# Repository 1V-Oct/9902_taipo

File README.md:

# TaiPo Micro MIDI Interface for 1V-Oct Family of Products
## Model: VO-9902 
## Version: 1.0

---
(C)2022 1V-Oct Limited

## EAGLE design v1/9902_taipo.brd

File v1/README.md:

# TaiPo Micro MIDI Interface for 1V-Oct Family of Products
## Model: VO-9902 
## Version: 1.0

This is simple MIDI interface for The Centre by 1V/Oct.

The 3.5mm jacks should be stereo jacks
PJ-301CM

Optocoupler:
TOSHIBA TLP2366 or can be the newer part TLP2361 (any other totem-pole octocoupler with 3.3V output can be used)

---
(C)2022 1V-Oct Limited

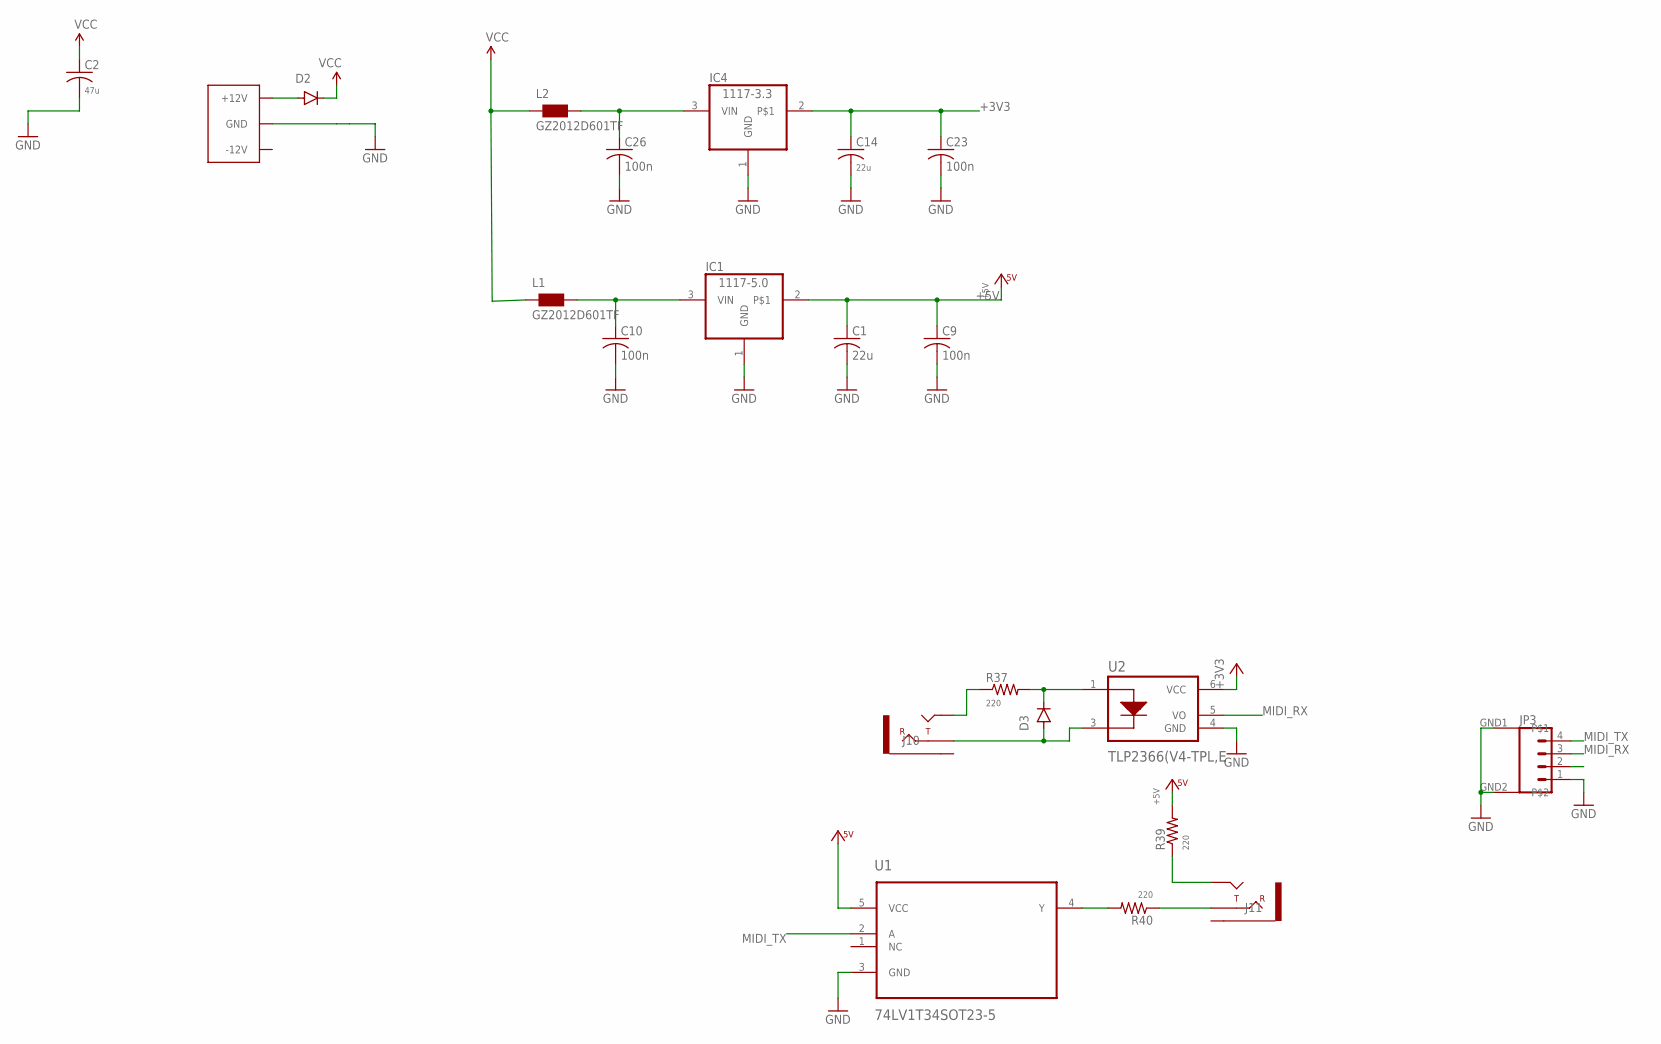
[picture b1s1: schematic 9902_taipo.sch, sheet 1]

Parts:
C1, C14: 22u; C0603
C2: 47u; C1206
C9, C10, C23, C26: 100n; C0402
D2: 1N5819HW; SOD123
D3: 1N4148; SOD323-R
IC1: 1117-5.0; SOT223
IC4: 1117-3.3; SOT223
J10, J11: PJ301CM
J21: EURO_POWER_LOCK; EURO_PWR_HEADER_FAT
JP3: M04A2001WF-4-SMD; A2001WF-NA-4
L1, L2: GZ2012D601TF; 0805
R37, R39, R40: 220; R0402
U1: 74LV1T34SOT23-5; SOT23-5__SOT95P280X145-5N
U2: TLP2366(V4-TPL,E; OPTO_TLP2366(V4-TPL,E

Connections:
+3V3: C14.1, C23.1, IC4.2, U2.6 (VCC)
+5V: C1.1, C9.1, IC1.2, R39.2, U1.5 (VCC)
DBG_PIN_2: JP3.2
GND: C1.2, C2.2, C9.2, C10.2, C14.2, C23.2, C26.2, IC1.1 (GND), IC4.1 (GND), J21.3 (GND), J21.4 (GND), J21.5 (GND), J21.6 (GND), J21.7 (GND), J21.8 (GND), JP3.1, JP3.GND1, JP3.GND2, U1.3 (GND), U2.4 (GND)
MIDI_RX: JP3.3, U2.5 (VO)
MIDI_TX: JP3.4, U1.2 (A)
unnamed: R40.2, U1.4 (Y)
unnamed: D3.C, R37.2, U2.1 (ANODE)
unnamed: D3.A, J10.P$2 (RING), U2.3 (CATHODE)
unnamed: J10.P$3 (TIP), R37.1
unnamed: J11.P$3 (TIP), R39.1
unnamed: J11.P$2 (RING), R40.1
unnamed: C10.1, IC1.3 (VIN), L1.2
unnamed: D2.A, J21.9 (+12V), J21.10 (+12V)
unnamed: C26.1, IC4.3 (VIN), L2.2
VCC: C2.1, D2.C, L1.1, L2.1

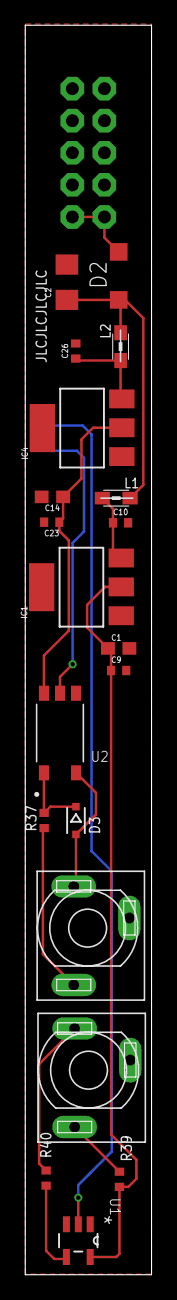
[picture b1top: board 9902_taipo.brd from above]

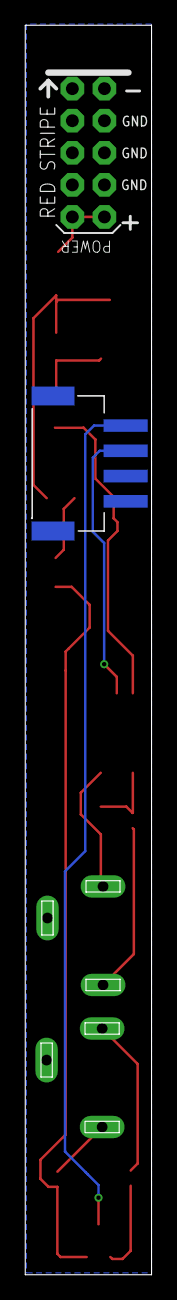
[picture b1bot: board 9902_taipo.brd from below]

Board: 2 copper layers, 9.9 x 98.9 mm, 22 parts (2 on the bottom side), 15 nets.

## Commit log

2022-05-16 V1 Design
2022-05-16 Resized for JLCPCB price optimisation
2022-05-16 JLCPCB Production Files
2022-05-16 Added preview files
2022-05-16 Cleanup with README
2022-05-16 Added Schematic
